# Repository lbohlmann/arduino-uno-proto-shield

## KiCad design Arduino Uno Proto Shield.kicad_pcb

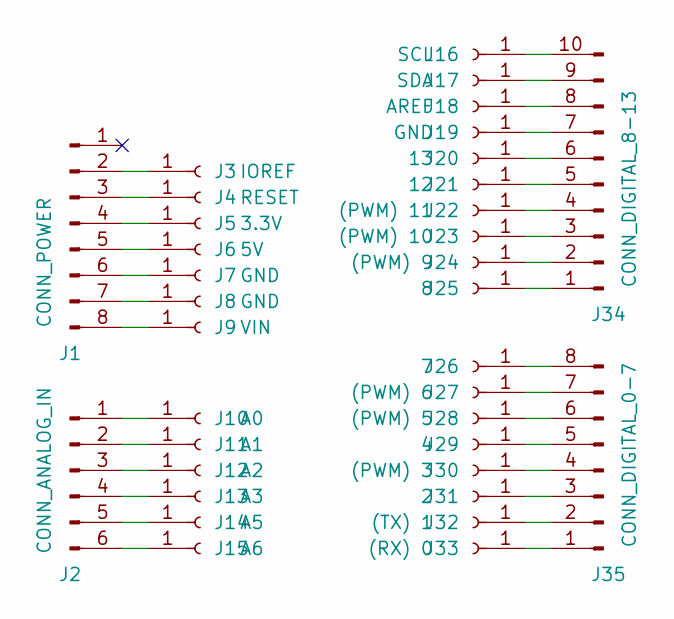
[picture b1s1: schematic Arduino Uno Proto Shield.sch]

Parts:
J1: CONN_POWER; PinHeader_1x08_P2.54mm_Vertical
J2: CONN_ANALOG_IN; PinHeader_1x06_P2.54mm_Vertical
J3: IOREF; SolderWirePad_1x01_Drill0.8mm
J4: RESET; SolderWirePad_1x01_Drill0.8mm
J5: 3.3V; SolderWirePad_1x01_Drill0.8mm
J6: 5V; SolderWirePad_1x01_Drill0.8mm
J7, J8, J19: GND; SolderWirePad_1x01_Drill0.8mm
J9: VIN; SolderWirePad_1x01_Drill0.8mm
J10: A0; SolderWirePad_1x01_Drill0.8mm
J11: A1; SolderWirePad_1x01_Drill0.8mm
J12: A2; SolderWirePad_1x01_Drill0.8mm
J13: A3; SolderWirePad_1x01_Drill0.8mm
J14: A5; SolderWirePad_1x01_Drill0.8mm
J15: A6; SolderWirePad_1x01_Drill0.8mm
J16: SCL; SolderWirePad_1x01_Drill0.8mm
J17: SDA; SolderWirePad_1x01_Drill0.8mm
J18: AREF; SolderWirePad_1x01_Drill0.8mm
J20: 13; SolderWirePad_1x01_Drill0.8mm
J21: 12; SolderWirePad_1x01_Drill0.8mm
J22: (PWM) 11; SolderWirePad_1x01_Drill0.8mm
J23: (PWM) 10; SolderWirePad_1x01_Drill0.8mm
J24: (PWM) 9; SolderWirePad_1x01_Drill0.8mm
J25: 8; SolderWirePad_1x01_Drill0.8mm
J26: 7; SolderWirePad_1x01_Drill0.8mm
J27: (PWM) 6; SolderWirePad_1x01_Drill0.8mm
J28: (PWM) 5; SolderWirePad_1x01_Drill0.8mm
J29: 4; SolderWirePad_1x01_Drill0.8mm
J30: (PWM) 3; SolderWirePad_1x01_Drill0.8mm
J31: 2; SolderWirePad_1x01_Drill0.8mm
J32: (TX) 1; SolderWirePad_1x01_Drill0.8mm
J33: (RX) 0; SolderWirePad_1x01_Drill0.8mm
J34: CONN_DIGITAL_8-13; PinHeader_1x10_P2.54mm_Vertical
J35: CONN_DIGITAL_0-7; PinHeader_1x08_P2.54mm_Vertical

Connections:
unnamed: J1.2, J3.1
unnamed: J1.3, J4.1
unnamed: J1.4, J5.1
unnamed: J1.5, J6.1
unnamed: J1.6, J7.1
unnamed: J1.7, J8.1
unnamed: J1.8, J9.1
unnamed: J2.1, J10.1
unnamed: J2.2, J11.1
unnamed: J2.3, J12.1
unnamed: J2.4, J13.1
unnamed: J2.5, J14.1
unnamed: J2.6, J15.1
unnamed: J16.1, J34.10
unnamed: J17.1, J34.9
unnamed: J18.1, J34.8
unnamed: J19.1, J34.7
unnamed: J20.1, J34.6
unnamed: J21.1, J34.5
unnamed: J22.1, J34.4
unnamed: J23.1, J34.3
unnamed: J24.1, J34.2
unnamed: J25.1, J34.1
unnamed: J26.1, J35.8
unnamed: J27.1, J35.7
unnamed: J28.1, J35.6
unnamed: J29.1, J35.5
unnamed: J30.1, J35.4
unnamed: J31.1, J35.3
unnamed: J32.1, J35.2
unnamed: J33.1, J35.1

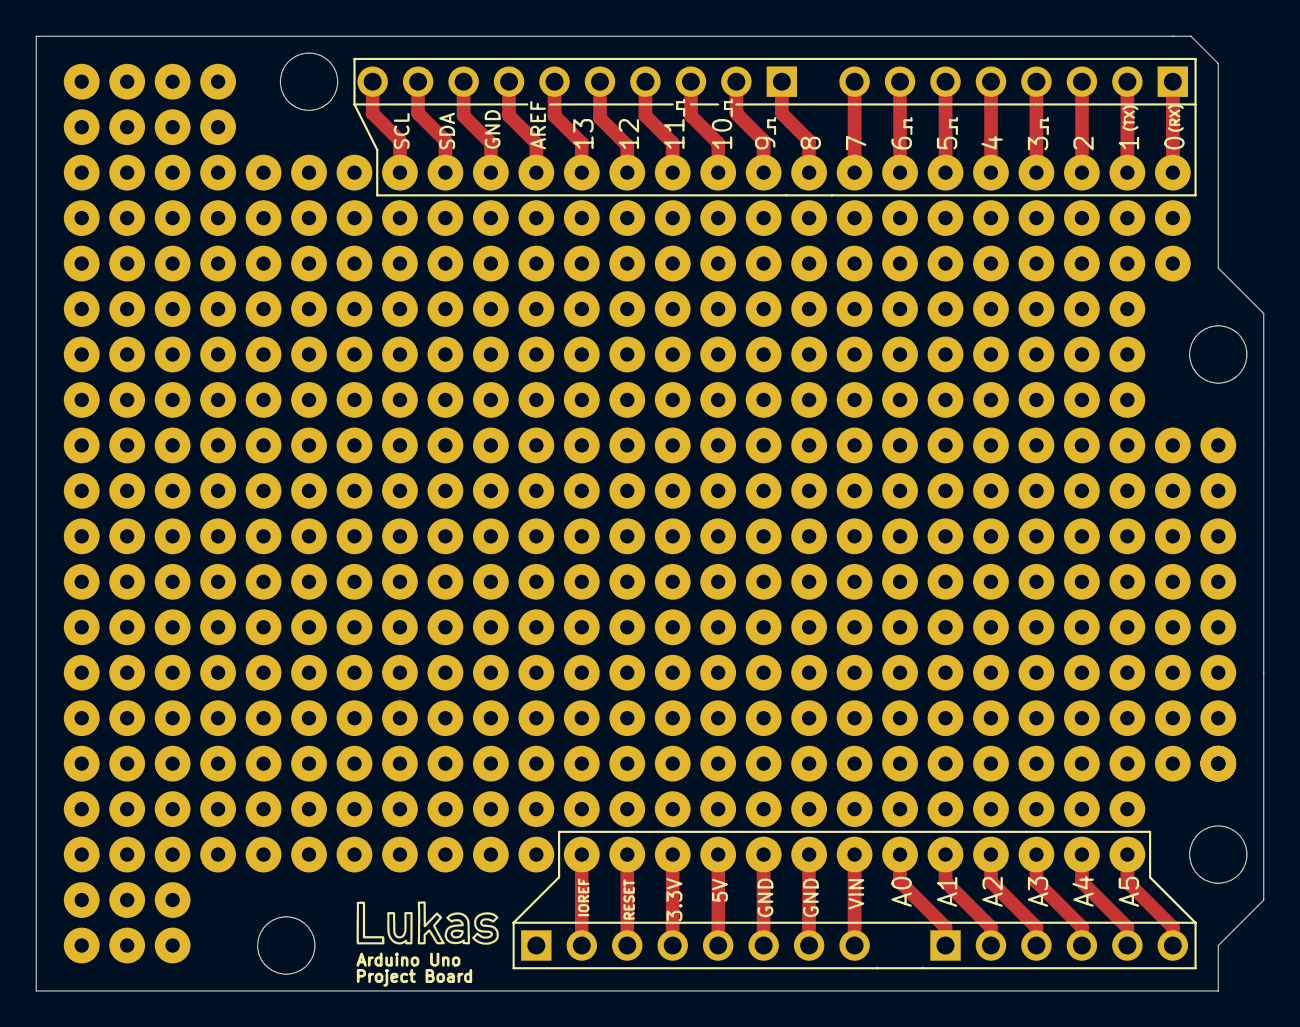
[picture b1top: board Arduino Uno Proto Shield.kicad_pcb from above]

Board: 2 copper layers, 68.6 x 53.3 mm, 35 parts (0 on the bottom side), 31 nets.

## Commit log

2021-02-05 Import KiCAD project
2021-02-13 Fix mounting hole placement
